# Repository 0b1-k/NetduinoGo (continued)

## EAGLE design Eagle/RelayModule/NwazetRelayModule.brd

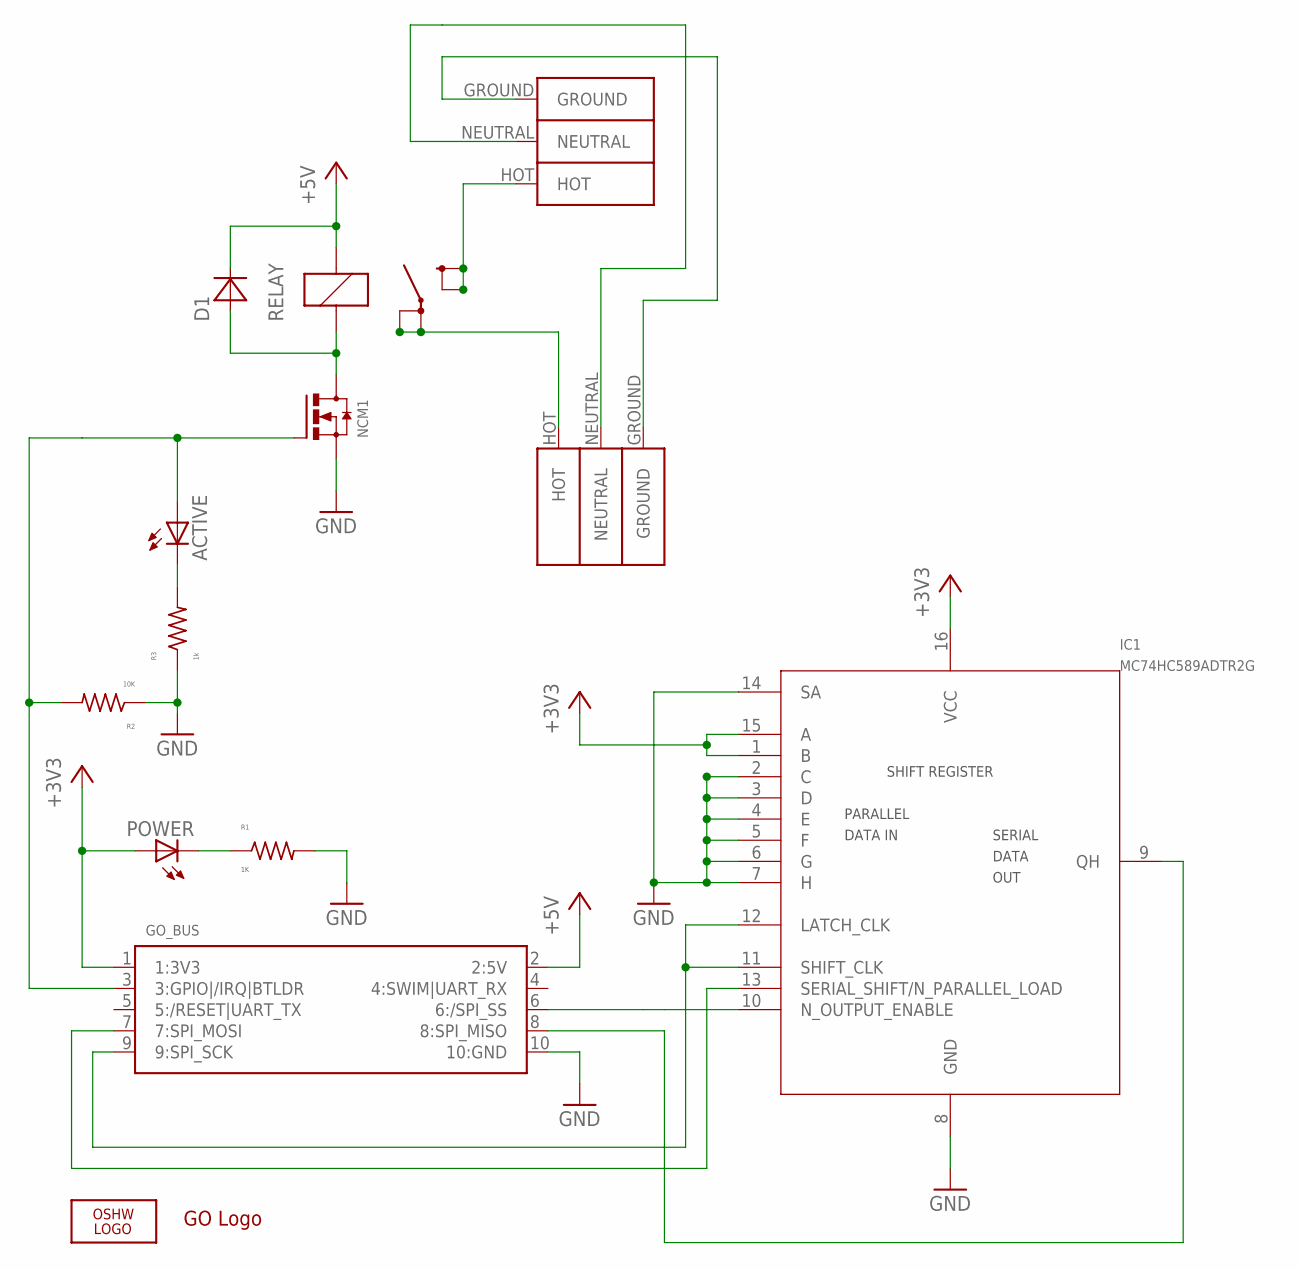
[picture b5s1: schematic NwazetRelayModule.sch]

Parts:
ACTIVE: LITEON_WHITE_LED_0805; 0805
D1: DIODE_POWERDI_323; DIODE_POWER_DI_323
GO_BUS: GO_CONNECTOR; FCI-1.27X1.27MM_10PIN_HEADER_SHROUDED_SMT
IC1: MC74HC589ADTR2G
LOGO1: OSHW_LOGO_FILLX0100-NT; OSHW_FILLX100_NOTEXT
NCM1: PHILIPS_2N7002F_N_CHANNEL_MOSFET; SOT23
POWER: LITEON_WHITE_LED_0805; 0805
R1: 1K; 0805
R2: 10K; 0805
R3: 1k; 0805
RELAY: SCHRACK_POWER_PCB_RELAY_RZ_16A_NO; SCHRACK_POWER_PCB_RELAY_RZ_16A
T1, T2: PHOENIX_WIRE_CONTACT_3_POSITIONS; WIRE_CONTACT_3_POSITIONS
U$8: GO_LOGO

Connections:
+3V3: GO_BUS.1 (1:3V3), IC1.1 (B), IC1.15 (A), IC1.16 (VCC), POWER.A
+5V: D1.CATHODE (C), GO_BUS.2 (2:5V), RELAY.COIL_A1
GND: GO_BUS.10 (10:GND), IC1.2 (C), IC1.3 (D), IC1.4 (E), IC1.5 (F), IC1.6 (G), IC1.7 (H), IC1.8 (GND), IC1.14 (SA), NCM1.2_SOURCE (SOURCE), R1.K (2), R2.A (1), R3.A (1)
HOT_T1: RELAY.11A_LOAD, RELAY.11B_LOAD, T1.HOT
HOT_T2: RELAY.14A_LOAD, RELAY.14B_LOAD, T2.HOT
unnamed: ACTIVE.A, GO_BUS.3 (3:GPIO|/IRQ|BTLDR), NCM1.1_GATE (GATE), R2.K (2)
unnamed: ACTIVE.K (C), R3.K (2)
unnamed: GO_BUS.9 (9:SPI_SCK), IC1.11 (SHIFT_CLK), IC1.12 (LATCH_CLK)
unnamed: GO_BUS.7 (7:SPI_MOSI), IC1.13 (SERIAL_SHIFT/N_PARALLEL_LOAD)
unnamed: GO_BUS.6 (6:/SPI_SS), IC1.10 (N_OUTPUT_ENABLE)
unnamed: GO_BUS.8 (8:SPI_MISO), IC1.9 (QH)
unnamed: POWER.K (C), R1.A (1)
unnamed: D1.ANODE (A), NCM1.3_DRAIN (DRAIN), RELAY.COIL_A2
unnamed: T1.GROUND, T2.GROUND
unnamed: T1.NEUTRAL, T2.NEUTRAL

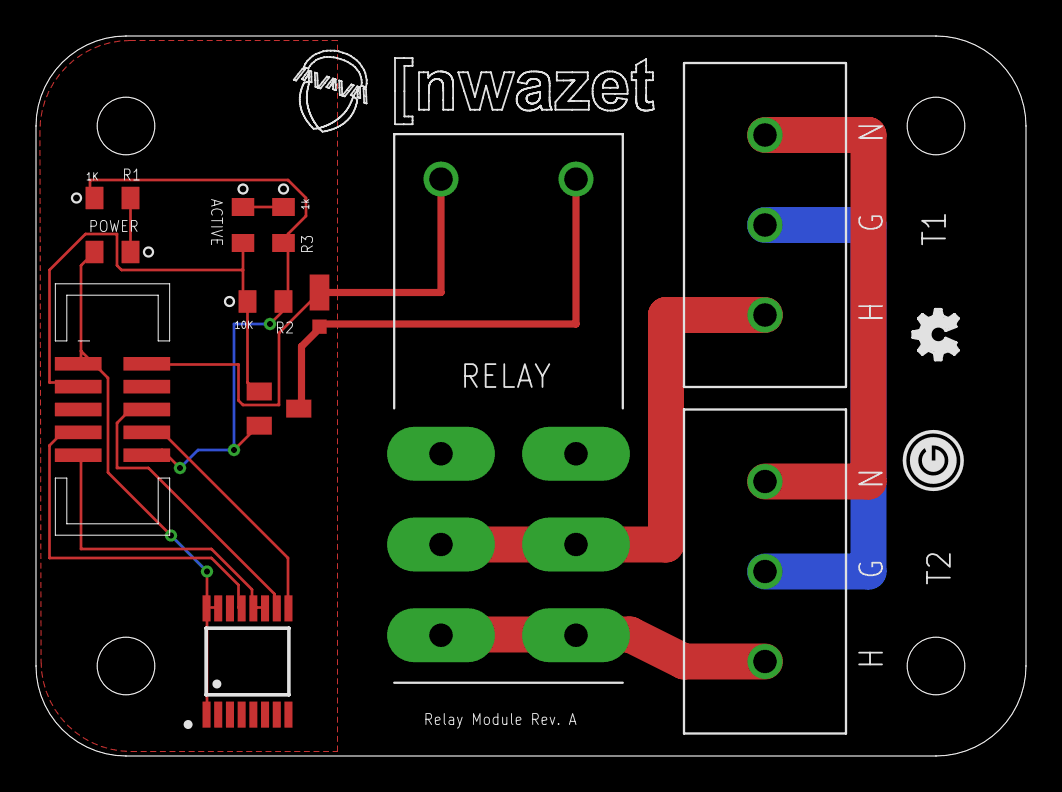
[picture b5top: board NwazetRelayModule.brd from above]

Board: 2 copper layers, 55.0 x 40.0 mm, 14 parts (0 on the bottom side), 15 nets.

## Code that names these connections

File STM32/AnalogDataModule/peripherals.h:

#ifndef _INC_Peripherals_
  #define _INC_Peripherals_

// SPI2 port/pin aliases
#define SPI2_PORT       GPIOB
#define SPI2_NSS_PIN    GPIO_Pin_12
#define SPI2_SCK_PIN    GPIO_Pin_13
#define SPI2_MISO_PIN   GPIO_Pin_14
#define SPI2_MOSI_PIN   GPIO_Pin_15

// SPI2 alternate function 0 pin sources
#define SPI2_NSS_PIN_SOURCE    GPIO_PinSource12
#define SPI2_SCK_PIN_SOURCE    GPIO_PinSource13
#define SPI2_MISO_PIN_SOURCE   GPIO_PinSource14
#define SPI2_MOSI_PIN_SOURCE   GPIO_PinSource15

// Go! Bus /IRQ port/pin aliases
#define GO_BUS_IRQ_PORT         GPIOD
#define GO_BUS_IRQ_PIN          GPIO_Pin_2
#define GOBUS_GPIO_SPEED        GPIO_Speed_50MHz

// Led Controller port/pin aliases
#define SR_CLOCK_PORT           GPIOF
#define SR_CLEAR_PORT           GPIOF
#define SR_LATCH_PORT           GPIOC
#define SR_OUTPUT_ENABLE_PORT   GPIOC
#define SR_DATA_IN_PORT         GPIOC

#define SR_CLEAR_PIN            GPIO_Pin_4
#define SR_CLOCK_PIN            GPIO_Pin_5
#define SR_LATCH_PIN            GPIO_Pin_10
#define SR_OUTPUT_ENABLE_PIN    GPIO_Pin_11
#define SR_DATA_IN_PIN          GPIO_Pin_12
#define SR_GPIO_SPEED           GPIO_Speed_10MHz

// I2C LED pin aliases
#define I2C2_LED_PORT           GPIOB
#define I2C2_LED                GPIO_Pin_2
#define I2C2_LED_GPIO_SPEED     GPIO_Speed_10MHz

// SD LED pin aliases
#define SD_LED_PORT             GPIOC
#define SD_LED                  GPIO_Pin_6
#define SD_LED_GPIO_SPEED       GPIO_Speed_10MHz

// UART1 LED pin aliases
#define USART_LED_PORT          GPIOC
#define USART_LED               GPIO_Pin_7
#define USART_LED_GPIO_SPEED    GPIO_Speed_10MHz

// Digital GPIOs aliases
#define DIGITAL_GPIO_SPEED      GPIO_Speed_50MHz

#define D0_PORT                 GPIOB
#define D0_PIN                  GPIO_Pin_9
#define D0_TIMER                TIM17
#define D0_TIMER_CHANNEL        TIM_Channel_1
#define D0_TIMER_ALT_FUNCTION   GPIO_AF_2
#define D0_TIMER_PIN_SOURCE     GPIO_PinSource9
#define D0_EXTI_PORT_SOURCE     EXTI_PortSourceGPIOB
#define D0_EXTI_PIN_SOURCE      EXTI_PinSource9
#define D0_EXTI_LINE            EXTI_Line9

#define D1_PORT                 GPIOB
#define D1_PIN                  GPIO_Pin_8
#define D1_TIMER                TIM16
#define D1_TIMER_CHANNEL        TIM_Channel_1
#define D1_TIMER_ALT_FUNCTION   GPIO_AF_2
#define D1_TIMER_PIN_SOURCE     GPIO_PinSource8
#define D1_EXTI_PORT_SOURCE     EXTI_PortSourceGPIOB
#define D1_EXTI_PIN_SOURCE      EXTI_PinSource8
#define D1_EXTI_LINE            EXTI_Line8

#define D2_PORT                 GPIOB
#define D2_PIN                  GPIO_Pin_10
#define D2_TIMER                TIM2
#define D2_TIMER_CHANNEL        TIM_Channel_3
#define D2_TIMER_ALT_FUNCTION   GPIO_AF_2
#define D2_TIMER_PIN_SOURCE     GPIO_PinSource10
#define D2_EXTI_PORT_SOURCE     EXTI_PortSourceGPIOB
#define D2_EXTI_PIN_SOURCE      EXTI_PinSource10
#define D2_EXTI_LINE            EXTI_Line10

#define D3_PORT                 GPIOB
#define D3_PIN                  GPIO_Pin_11
#define D3_TIMER                TIM2
#define D3_TIMER_CHANNEL        TIM_Channel_4
#define D3_TIMER_ALT_FUNCTION   GPIO_AF_2
#define D3_TIMER_PIN_SOURCE     GPIO_PinSource11
#define D3_EXTI_PORT_SOURCE     EXTI_PortSourceGPIOB
#define D3_EXTI_PIN_SOURCE      EXTI_PinSource11
#define D3_EXTI_LINE            EXTI_Line11

#define D4_PORT                 GPIOA
#define D4_PIN                  GPIO_Pin_4
#define D4_TIMER                TIM14
#define D4_TIMER_CHANNEL        TIM_Channel_1
#define D4_TIMER_ALT_FUNCTION   GPIO_AF_4
#define D4_TIMER_PIN_SOURCE     GPIO_PinSource4
#define D4_EXTI_PORT_SOURCE     EXTI_PortSourceGPIOA
#define D4_EXTI_PIN_SOURCE      EXTI_PinSource4
#define D4_EXTI_LINE            EXTI_Line0

#define D5_PORT                 GPIOB
#define D5_PIN                  GPIO_Pin_3
#define D5_TIMER                TIM2
#define D5_TIMER_CHANNEL        TIM_Channel_2
#define D5_TIMER_ALT_FUNCTION   GPIO_AF_2
#define D5_TIMER_PIN_SOURCE     GPIO_PinSource3
#define D5_EXTI_PORT_SOURCE     EXTI_PortSourceGPIOB
#define D5_EXTI_PIN_SOURCE      EXTI_PinSource3
#define D5_EXTI_LINE            EXTI_Line3

#define D6_PORT                 GPIOB
#define D6_PIN                  GPIO_Pin_4
#define D6_TIMER                TIM3
#define D6_TIMER_CHANNEL        TIM_Channel_1
#define D6_TIMER_ALT_FUNCTION   GPIO_AF_1
#define D6_TIMER_PIN_SOURCE     GPIO_PinSource4
#define D6_EXTI_PORT_SOURCE     EXTI_PortSourceGPIOB
#define D6_EXTI_PIN_SOURCE      EXTI_PinSource4
#define D6_EXTI_LINE            EXTI_Line4

#define D7_PORT                 GPIOB
#define D7_PIN                  GPIO_Pin_5
#define D7_TIMER                TIM3
#define D7_TIMER_CHANNEL        TIM_Channel_2
#define D7_TIMER_ALT_FUNCTION   GPIO_AF_1
#define D7_TIMER_PIN_SOURCE     GPIO_PinSource5
#define D7_EXTI_PORT_SOURCE     EXTI_PortSourceGPIOB
#define D7_EXTI_PIN_SOURCE      EXTI_PinSource5
#define D7_EXTI_LINE            EXTI_Line5

#define DEFAULT_PERIOD_HZ       1000
#define DEFAULT_TIMER_PERIOD    (SystemCoreClock / DEFAULT_PERIOD_HZ ) - 1

// SD card GPIO aliases
#define SD_SPI                          SPI1

#define SD_GPIO_SPEED                   GPIO_Speed_10MHz

#define SD_SPI_SCK_PIN                  GPIO_Pin_5
#define SD_SPI_SCK_GPIO_PORT            GPIOA
#define SD_SPI_SCK_SOURCE               GPIO_PinSource5
#define SD_SPI_SCK_AF                   GPIO_AF_0

#define SD_SPI_MOSI_PIN                 GPIO_Pin_7
#define SD_SPI_MOSI_GPIO_PORT           GPIOA
#define SD_SPI_MOSI_SOURCE              GPIO_PinSource7
#define SD_SPI_MOSI_AF                  GPIO_AF_0

#define SD_SPI_MISO_PIN                 GPIO_Pin_6
#define SD_SPI_MISO_GPIO_PORT           GPIOA
#define SD_SPI_MISO_SOURCE              GPIO_PinSource6
#define SD_SPI_MISO_AF                  GPIO_AF_0

#define SD_CS_PIN                       GPIO_Pin_15
#define SD_CS_GPIO_PORT                 GPIOA

#define SD_DETECT_PIN                   GPIO_Pin_8
#define SD_DETECT_GPIO_PORT             GPIOC

#define SD_WRITE_PROTECT_PIN            GPIO_Pin_9
#define SD_WRITE_PROTECT_GPIO_PORT      GPIOC

#define SD_DETECT_EXTI_LINE             EXTI_Line8
#define SD_DETECT_EXTI_PIN_SOURCE       EXTI_PinSource8
#define SD_DETECT_EXTI_PORT_SOURCE      EXTI_PortSourceGPIOC
#define SD_DETECT_EXTI_IRQn             EXTI4_15_IRQHandler

// USART GPIO aliases
#define USART_PORT                      USART2
#define USART_GPIO_PORT                 GPIOA
#define USART_GPIO_SPEED                GPIO_Speed_50MHz
#define USART_CTS_PIN                   GPIO_Pin_0
#define USART_RTS_PIN                   GPIO_Pin_1
#define USART_TX_PIN                    GPIO_Pin_2
#define USART_RX_PIN                    GPIO_Pin_3
#define USART_CTS_PIN_SOURCE            GPIO_PinSource0
#define USART_RTS_PIN_SOURCE            GPIO_PinSource1
#define USART_TX_PIN_SOURCE             GPIO_PinSource2
#define USART_RX_PIN_SOURCE             GPIO_PinSource3
#define USART_AF                        GPIO_AF_1
#define USART_DEFAULT_BAUD_RATE         115200

// I2C GPIO aliases
#define I2C_GPIO_SPEED                  GPIO_Speed_50MHz
#define I2C_SCL_PIN                     GPIO_Pin_6
#define I2C_SDA_PIN                     GPIO_Pin_7
#define I2C_SCL_PIN_SOURCE              GPIO_PinSource6
#define I2C_SDA_PIN_SOURCE              GPIO_PinSource7
#define I2C_GPIO_PORT                   GPIOF
#define I2C_AF                          GPIO_AF_0
#define I2C_PERIPHERAL                  I2C2

void initPeripherals();

#endif

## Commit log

2015-04-08 Netduino Go hardware and software projects
